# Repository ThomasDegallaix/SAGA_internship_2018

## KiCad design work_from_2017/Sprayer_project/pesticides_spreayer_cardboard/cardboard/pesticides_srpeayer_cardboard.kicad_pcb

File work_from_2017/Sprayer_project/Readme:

- The motor controller script given here is exactly the same that is uploaded on the motor controller. TPDO1 is set on 40ms, autoscripting enabled.

- Due to a design mistake, the circuit board's pins to connect to the motor controller are inverted, the problem can be avoided by inverting the female PCB connector, placing it on the circuit board's bottom; and by twisting 180° the ribbon flat cable.
Also, the pins 4 and 5 of the INA122 (see joined datasheet) shall be connected to ground, on the circuit board the design made connect only the 5th pin to ground. The problem has been avoided by soldering a resistor's cutted metal between the two pins under the circuit board.

-You'll find all the ROS code on the robot, all modifications had been enclosed by:

//PPPPPPPPPPPPPPPPPPPPPPPPPPPPPPPPPPPPPPPPPPPPPPPPPPPPPPPPPPPPPPP
// EDIT Author: Pierre Pezelet E-mail: pierre.pezelet@hotmail.com
// PURPOSE: Spraying module integration - Aug 2017

   *CODE*

// END EDIT
//PPPPPPPPPPPPPPPPPPPPPPPPPPPPPPPPPPPPPPPPPPPPPPPPPPPPPPPPPPPPPPP

Added package:
- ~/catkin_ws/src/sprayer_driver

Added files:
- ~/catkin_ws/src/can_devices/common/src/RoboteqSdc2130S.cpp
- ~/catkin_ws/src/can_devices/common/include/RoboteqSdc2130S.h

Modified files:
- ~/catkin_ws/src/base_driver/common/src/CanCtrlPltf.cpp
- ~/catkin_ws/src/base_driver/common/include/CanCtrlPltf.h
- ~/catkin_ws/src/base_driver/ros/src/thorvald_base_drive_chain.cpp
- ~/catkin_ws/src/teleop_xbox/src/teleop_xbox.cpp

TODO: Cleaning the code + further developpement on the motor controller feedback (temperature, communication flag, ect...) for now it is supposed that the motor controller is always OK.

-About the mechanics:
Verify that the pump's screws aren't loosens after a run in the field.
When I left I didn't tighten these screws be sure to do it.
To take the module off the robot: 
Unplug the metal connector, pull the black connector, and lift the module away. Reverse process to mount it.

-About the Kicad project name, I'm conscious now of what cardboard means, and of the spelling mistake on sprayer, but for a time saving and kicad project integrity purposes, I prefered not changing the name!

If think that's all you need to know; enjoy the sprayer and if you need anything don't hesitate to contact me on messenger or pierre.pezelet@isen.yncrea.fr :)

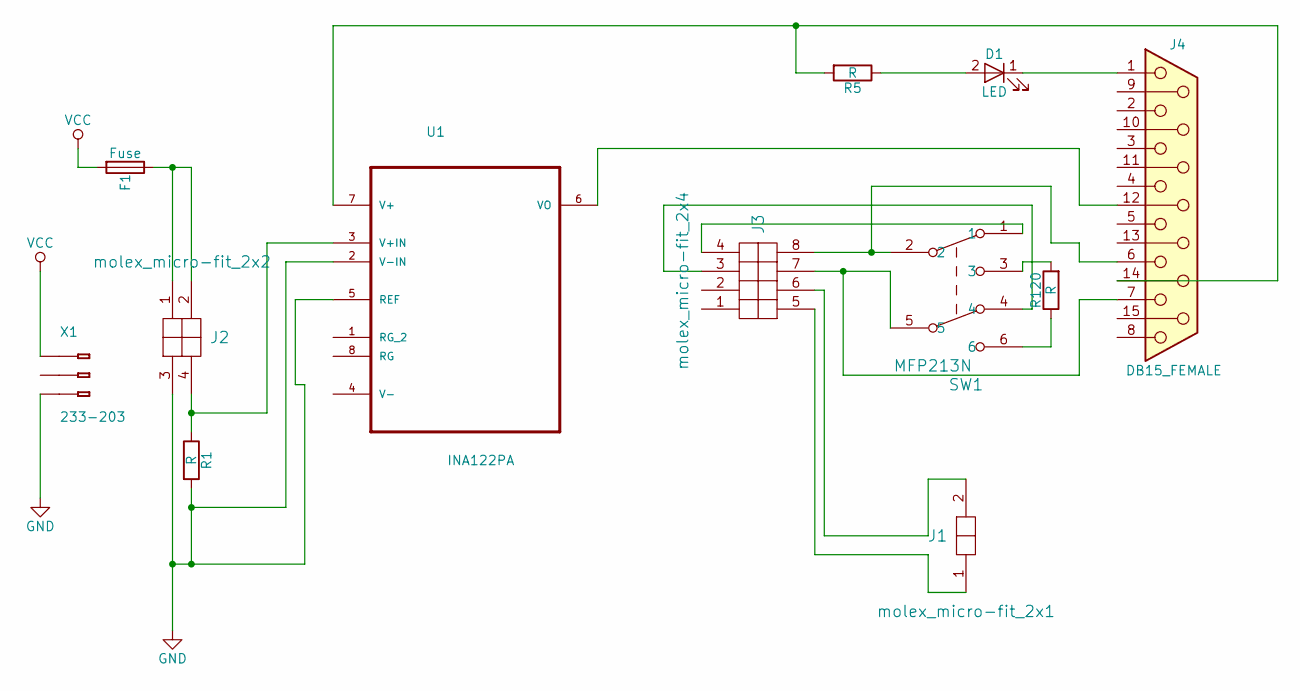
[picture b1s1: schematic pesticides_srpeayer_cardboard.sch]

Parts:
D1: LED; LED_D3.0mm
F1: Fuse; Fuseholder_ATO_Blade_littlefuse_Pudenz_2_Pin
J1: molex_micro-fit_2x1; molex_micro-fit_43045-0212
J2: molex_micro-fit_2x2; molex_micro-fit_43045-0412
J3: molex_micro-fit_2x4; molex_micro-fit_43045-0812
J4: DB15_FEMALE; DB15FC
R1, R5, R120: R; R_Axial_DIN0207_L6.3mm_D2.5mm_P10.16mm_Horizontal
SW1: MFP213N; MFP213N_DPDT
U1: INA122PA; DIP254P762X508-8
X1: 233-203

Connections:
GND: J2.3, R1.2, U1.2 (V-IN), U1.5 (REF), X1.B3 (B-3)
unnamed: D1.1 (K), J4.1
unnamed: D1.2 (A), R5.1
unnamed: F1.1, J2.1, J2.2
unnamed: J1.1, J3.5
unnamed: J1.2, J3.6
unnamed: J2.4, R1.1, U1.3 (V+IN)
unnamed: J3.3, SW1.4
unnamed: J3.4, SW1.1
unnamed: J3.7, J4.7, SW1.5
unnamed: J3.8, J4.6, SW1.2
unnamed: J4.12, U1.6 (VO)
unnamed: J4.14, R5.2, U1.7 (V+)
unnamed: R120.1, SW1.6
unnamed: R120.2, SW1.3
VCC: F1.2, X1.B1 (B-1)

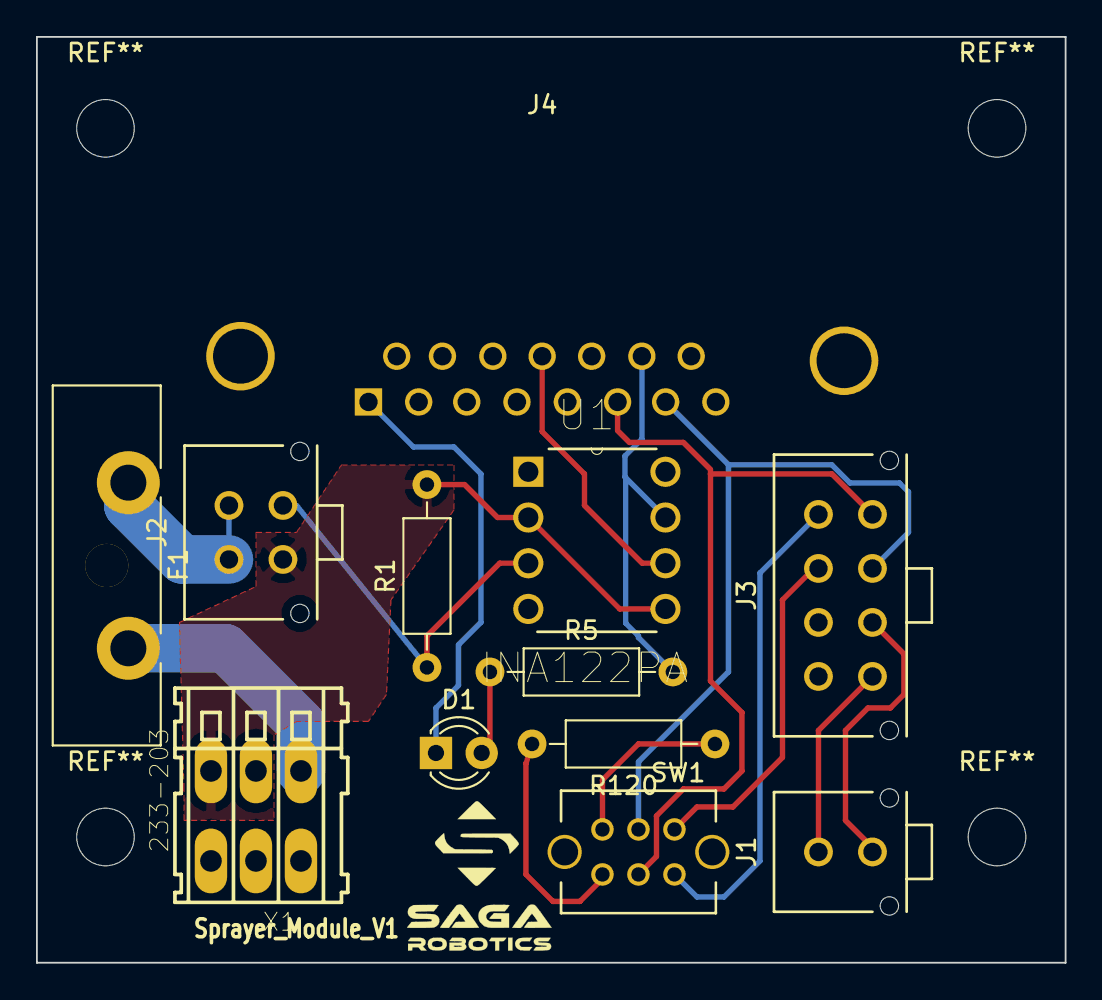
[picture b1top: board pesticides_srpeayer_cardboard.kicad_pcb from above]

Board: 2 copper layers, 57.1 x 51.4 mm, 12 parts (0 on the bottom side), 16 nets.

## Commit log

2018-05-15 Sprayer Script update
2018-05-15 Sprayer script
2018-05-15 Script Update
2018-05-15 Scipt Sprayer Update
2018-05-16 New Sprayer Controller File
2018-05-16 new sprayer script update
2018-05-18 sprayer node v0.1
2018-05-18 sprayer node V2
2018-05-19 Little changes on sprayerV2
2018-05-22 Infos about the robot environment
2018-05-22 Implementation of the good data format in sprayerV2
2018-05-22 Starting the use of a service combined with the sprayer node
2018-05-22 sprayerV3 + controller service, need some debugging
2018-05-22 Working version of sprayerV3 with a service
2018-05-23 SprayerV3: switch from global a variable for the request to a struct
2018-05-23 Minor modifications
2018-05-23 Minor changes
2018-05-23 sprayerV4 + sprayerControllerV2
2018-05-23 Remove duplicated directory
2018-05-23 Name changed
2018-05-24 Going for a version 5 using classes !
2018-05-24 Share with workspace
2018-05-24 Remove non used directory
2018-05-24 SprayerV5 (use of a class)
2018-05-25 SprayerV5 uses now the correct msg datatype + beginning of pressure enslavement
2018-05-29 New version of the sprayer pump script.
2018-05-29 Some improvements on sprayerV5
2018-05-29 Deletion of former scripts
2018-05-30 Maj on v5 by antoine Bedhome feedback
2018-05-30 Modification on v5 node and command.h
2018-05-30 Sprayerv5
2018-05-30 sprayer_controller service pay attention to the pump status
2018-05-31 onoff service, mode service, new version of the node sprayer
2018-05-31 Add dependencies in the makefile to make the package build correctly on another computer
2018-06-04 SprayerV5 + all services working
2018-06-05 Rate changement (1Hz to 10 Hz)
2018-06-06 Retrieve pressure in sprayerV5
2018-06-06 SprayerV6: Use of the flow and tora's velocity
2018-06-07 SprayerV6: implementation of new functionalities
2018-06-08 SprayerV6: some bugs need to be handled
2018-06-11 Some works on watering
2018-06-13 Watering task with action server/client
2018-06-14 Action client/server working with multithreaded spinner
2018-06-19 datasheets for the sprayer and the grass cutter
2018-06-21 More datasheets
2018-06-22 Some datasheets + thesis
2018-07-18 first commit of the grass cutter package
2018-07-23 Rasberry Navigations testcase
2018-07-26 Testcase for Rasberry topological navigation
